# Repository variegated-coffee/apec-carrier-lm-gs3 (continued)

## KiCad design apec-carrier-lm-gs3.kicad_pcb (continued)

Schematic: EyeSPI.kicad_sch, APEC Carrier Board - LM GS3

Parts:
C1, C4, C63: 10 uF, 50V, X7R; C_1206_3216Metric; Digikey 1276-6767-1-ND
J13: Conn_02x10_Odd_Even; IDC-Header_2x10_P2.54mm_Vertical
J17: Molex 525591853; CON_525591853_MOL; LCSC C3169221
R70, R71, R72: 47R; R_0603_1608Metric; LCSC C23182

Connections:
+3V3: C1.2, J13.17, J17.1 (Vcc); also elsewhere on the board
+5V: C63.1, J13.20; also elsewhere on the board
EYESPI_BL: J13.18, J17.2 (BACKLIGHT); also elsewhere on the board
EYESPI_BUSY_TE: J13.4, J17.16 (BUSY/TE); also elsewhere on the board
EYESPI_DC: J13.11, J17.7 (DC); also elsewhere on the board
EYESPI_DISP_CS: J13.9, J17.9 (DISP_CS); also elsewhere on the board
EYESPI_GP1: J13.1, J17.17 (GPIO1); also elsewhere on the board
EYESPI_GP2: J13.2, J17.18 (GPIO2); also elsewhere on the board
EYESPI_INT: J13.3, J17.15 (INT); also elsewhere on the board
EYESPI_MEM_CS: J13.7, J17.11 (MEM_CS); also elsewhere on the board
EYESPI_MISO: R72.2; also elsewhere on the board
EYESPI_MISO_POST_R: J13.14, J17.6 (MISO), R72.1
EYESPI_MOSI: R71.1; also elsewhere on the board
EYESPI_MOSI_POST_R: J13.13, J17.5 (MOSI), R71.2
EYESPI_RES: J13.12, J17.8 (RESET); also elsewhere on the board
EYESPI_SCK: R70.2; also elsewhere on the board
EYESPI_SCK_POST_R: J13.16, J17.4 (SCK), R70.1
EYESPI_SD_CS: J13.10, J17.10 (SD_CS); also elsewhere on the board
EYESPI_TS_CS: J13.8, J17.12 (TS_CS); also elsewhere on the board
GND: C1.1, C4.2, C63.2, J13.15, J17.3 (GND); also elsewhere on the board
QWIIC_SCL: J13.5, J17.13 (SCL); also elsewhere on the board
QWIIC_SDA: J13.6, J17.14 (SDA); also elsewhere on the board
VIN: C4.1, J13.19; also elsewhere on the board

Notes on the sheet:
EyeSPI Connector

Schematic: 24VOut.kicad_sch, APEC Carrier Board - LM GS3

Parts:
C53, C54: 22 uF, 50V, X7R; C_2220_5750Metric_Pad1.97x5.40mm_HandSolder; Digikey 445-C5750X7R1H226M250KBCT-ND
C55: 100 nF, 50V, X7R; C_0603_1608Metric; LCSC C14663
CN13, CN14: Conn_01x02; TE_280370-1; LCSC C86459; not fitted
D11, D13: SS2200; D_SMA; LCSC C14332
D17, D18: LED; LED_0402_1005Metric; LCSC C130724
Q11, Q12: IRFZ44N; TO-220-3_Vertical; Digikey IRFZ44NPBF-ND
Q28: BSS138DW; SOT-363_SC-70-6; LCSC C154900
R55, R56: 10K; R_0402_1005Metric; LCSC C25744
R64, R66: 100R; R_0402_1005Metric; LCSC C25076
R73, R74: 6R8; R_0603_1608Metric; LCSC C228038
R75, R76: 100K; R_0603_1608Metric; LCSC C422892
U16: ADuM3221; SOIC-8_3.9x4.9mm_P1.27mm; LCSC C208191

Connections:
12V_ISO: U16.8 (VDD2); also elsewhere on the board
24V_STEAM_OUT: Q28.2 (G), R56.1, U16.3 (VIB); also elsewhere on the board
24V_TEA_SOLENOID: Q28.5 (G), R55.2, U16.2 (VIA); also elsewhere on the board
+3V3: C55.2, R64.1, R66.1, U16.1 (VDD1); also elsewhere on the board
+24V: C53.1, C54.1, CN13.2, CN14.2, D11.1 (K), D13.1 (K); also elsewhere on the board
GND: C55.1, Q28.1 (S), Q28.4 (S), R55.1, R56.2, U16.4 (GND1); also elsewhere on the board
GNDPWR: C53.2, C54.2, Q11.3 (S), Q12.3 (S), R75.2, R76.1, U16.5 (GND2); also elsewhere on the board
unnamed: CN13.1, D13.2 (A), Q11.2 (D)
unnamed: CN14.1, D11.2 (A), Q12.2 (D)
unnamed: D17.2 (A), R64.2
unnamed: D17.1 (K), Q28.6 (D)
unnamed: D18.2 (A), R66.2
unnamed: D18.1 (K), Q28.3 (D)
unnamed: Q11.1 (G), R73.1, R75.1
unnamed: Q12.1 (G), R74.2, R76.2
unnamed: R74.1, U16.7 (VOA)
unnamed: R73.2, U16.6 (VOB)

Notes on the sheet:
U16 is an ADuM3221 drawn with the ADuM1200 symbol. The pinouts are the same (ADuM3220/ADuM3221 datasheet).
RP2350 erratum E9 and pull-downs R55, R56: The 10K pull-downs hold these outputs low despite E9. E9 (A2 stepping only) needs a pin's input buffer on, its output off and its voltage between the logic levels. After power-up or reset the input buffer is off, so the pull-down holds the pin low, and onc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

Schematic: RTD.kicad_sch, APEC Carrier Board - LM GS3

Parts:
C5, C7, C13, C15, C21, C26: 4.7nF, C0G; C_0805_2012Metric_Pad1.18x1.45mm_HandSolder; LCSC C338091
C6, C10, C14: 47nF, C0G; C_0805_2012Metric_Pad1.18x1.45mm_HandSolder; LCSC C2182212
C30: 47 uF, 25V; C_1206_3216Metric; LCSC C76659
J8, J11: Conn_01x04; TE_280371-2; Digikey A106401-ND
JP3, JP6, JP7, JP8: SolderJumper_2_Bridged; SolderJumper-2_P1.3mm_Bridged_RoundedPad1.0x1.5mm
JP4, JP9: SolderJumper_2_Open; SolderJumper-2_P1.3mm_Open_RoundedPad1.0x1.5mm
R5: 2K2 0.01%; R_0805_2012Metric_Pad1.20x1.40mm_HandSolder; LCSC C2089922
R6, R7, R18, R20: 4K99 0.1%; R_0805_2012Metric_Pad1.20x1.40mm_HandSolder; LCSC C864414
R9: 10K; R_0805_2012Metric_Pad1.20x1.40mm_HandSolder; LCSC C17414
R34: 0R; R_0805_2012Metric_Pad1.20x1.40mm_HandSolder; LCSC C17477

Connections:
+5VA: C30.1; also elsewhere on the board
ADC_AIN0: J11.4, JP3.1 (A); also elsewhere on the board
ADC_AIN1: C5.2, C6.1, R6.2; also elsewhere on the board
ADC_AIN2: C6.2, C7.1, R7.2; also elsewhere on the board
ADC_AIN3: JP4.1 (A); also elsewhere on the board
ADC_AIN8: J8.4, JP7.1 (A); also elsewhere on the board
ADC_AIN9: C13.2, C14.1, R18.2; also elsewhere on the board
ADC_AIN10: C14.2, C15.1, R20.2; also elsewhere on the board
ADC_AIN11: JP9.1 (A); also elsewhere on the board
ADC_REFN0: C10.2, C21.1, R34.1; also elsewhere on the board
ADC_REFP0: C10.1, C26.2, R9.1; also elsewhere on the board
GNDA: C5.1, C7.2, C13.1, C15.2, C21.2, C26.1, C30.2, R5.2, R34.2; also elsewhere on the board
unnamed: J8.2, JP8.2 (B), JP9.2 (B), R20.1
unnamed: J8.3, JP7.2 (B), R18.1
unnamed: J11.2, JP4.2 (B), JP6.2 (B), R7.1
unnamed: J11.3, JP3.2 (B), R6.1
REF_R: J8.1, J11.1, JP6.1 (A), JP8.1 (A), R5.1, R9.2

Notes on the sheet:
This is basically just the reference design from TI. This filter (~323 Hz) should be frequency matched to the filter on the reference resistor (~308 Hz).
These are both configured for a two-wire PT1000 measurement. To change to three-wire or four-wire, you can cut/solder jumpers according to SBAA275A. The filter resistors and capacitors should also be changed. Similarly, to change to PT100, you can change filter resistors and capacitors.
This is part of the reference design from TI. The values for the filter and the reference resistor should be selected to match the excitation current and filter frequency (330 Hz). R1A: R_Ref (R5) = 2K2. Inputs: 2 x 4K99 into 47 nF + 2 x 4.7 nF -> ~323 Hz. Reference: REFN0 straight to R5 (R34 = 0R,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

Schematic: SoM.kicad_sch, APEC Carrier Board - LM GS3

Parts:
C27, C29: 47 uF, 25V; C_1206_3216Metric; LCSC C76659
J25: BM03B-SRSS-TBLFSN; CONN_BM03B-SRSS-TBLFSN_JST; LCSC C160389
JP10: SolderJumper_3_Open; SolderJumper-3_P1.3mm_Open_RoundedPad1.0x1.5mm_NumberLabels
R46, R47: 100R; R_0402_1005Metric; LCSC C25076
SW3, SW4, SW5, SW6: B3FS-100xP; SW_SPST_Omron_B3FS-100xP; LCSC C231324
U1: APEC_SoM; APEC_SoM_SMD
U6: Femtoprobe; Femtoprobe SMT

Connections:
24V_STEAM_OUT: U1.19 (RP2350_GP5); also elsewhere on the board
24V_TEA_SOLENOID: U1.29 (RP2350_GP43); also elsewhere on the board
+3V3: C29.2, JP10.3 (B), U1.76 (3V3), U1.77 (3V3), U6.4 (3V3); also elsewhere on the board
+5V: C27.2, U1.85 (+5V), U1.86 (+5V); also elsewhere on the board
+5VA: U1.50 (5VA); also elsewhere on the board
ADC_AIN0: U1.41 (ADC_AIN0); also elsewhere on the board
ADC_AIN1: U1.42 (ADC_AIN1); also elsewhere on the board
ADC_AIN2: U1.43 (ADC_AIN2); also elsewhere on the board
ADC_AIN3: U1.44 (ADC_AIN3); also elsewhere on the board
ADC_AIN4: U1.45 (ADC_AIN4); also elsewhere on the board
ADC_AIN5: U1.46 (ADC_AIN5); also elsewhere on the board
ADC_AIN8: U1.53 (ADC_AIN8); also elsewhere on the board
ADC_AIN9: U1.54 (ADC_AIN9); also elsewhere on the board
ADC_AIN10: U1.55 (ADC_AIN10); also elsewhere on the board
ADC_AIN11: U1.56 (ADC_AIN11); also elsewhere on the board
ADC_REFN0: U1.52 (ADC_REFN0); also elsewhere on the board
ADC_REFP0: U1.51 (ADC_REFP0); also elsewhere on the board
ADC_REFP1: U1.47 (ADC_AIN6_REFP1); also elsewhere on the board
AIN_POT_1_2V5: U1.25 (RP2350_GP47); also elsewhere on the board
AIN_POT_2_2V5: U1.26 (RP2350_GP46); also elsewhere on the board
APEC_USB_UPSTREAM_DN: U1.89 (USB_UPSTREAM_DN); also elsewhere on the board
APEC_USB_UPSTREAM_DP: U1.88 (USB_UPSTREAM_DP); also elsewhere on the board
AUX1: U1.32 (RP2350_GP40); also elsewhere on the board
BREW_BOILER_EN: U1.61 (RP2350_GP37); also elsewhere on the board
CIN3: U1.37 (CIN3); also elsewhere on the board
CIN4: U1.36 (CIN4); also elsewhere on the board
ESP32_EN: SW5.1, U1.104 (ESP32_EN)
ESP32_GP0: U1.1 (ESP32_GP0); also elsewhere on the board
ESP32_GP1: U1.2 (ESP32_GP1); also elsewhere on the board
ESP32_GPIO9: SW6.1, U1.103 (ESP32_GPIO9)
ESP32_U0RX: U1.3 (ESP32_U0RXD), U6.6 (UART_TX)
ESP32_U0TX: U1.4 (ESP32_U0TXD), U6.5 (UART_RX)
EYESPI_BL: U1.23 (RP2350_GP1); also elsewhere on the board
EYESPI_BUSY_TE: U1.6 (RP2350_GP22); also elsewhere on the board
EYESPI_DC: U1.18 (RP2350_GP6); also elsewhere on the board
EYESPI_DISP_CS: U1.16 (RP2350_GP12); also elsewhere on the board
EYESPI_GP1: U1.10 (RP2350_GP18); also elsewhere on the board
EYESPI_GP2: U1.9 (RP2350_GP19); also elsewhere on the board
EYESPI_INT: U1.7 (RP2350_GP21); also elsewhere on the board
EYESPI_MEM_CS: U1.14 (RP2350_GP14); also elsewhere on the board
EYESPI_MISO: U1.20 (RP2350_GP4); also elsewhere on the board
EYESPI_MOSI: U1.21 (RP2350_GP3); also elsewhere on the board
EYESPI_RES: U1.17 (RP2350_GP7); also elsewhere on the board
EYESPI_SCK: U1.22 (RP2350_GP2); also elsewhere on the board
EYESPI_SD_CS: U1.15 (RP2350_GP13); also elsewhere on the board
EYESPI_TS_CS: U1.13 (RP2350_GP15); also elsewhere on the board
FDC_SHLD1: U1.40 (C_SHIELD_1); also elsewhere on the board
FDC_SHLD2: U1.35 (C_SHIELD_2); also elsewhere on the board
FEMTOPROBE_USB_DN: U1.95 (USB_PORT4_DN), U6.2 (USB_D-)
FEMTOPROBE_USB_DP: U1.94 (USB_PORT4_DP), U6.3 (USB_D+)
FG_DIRECTION_3V3: U1.63 (RP2350_GP35); also elsewhere on the board
FG_SPEED_IN_3V3: U1.28 (RP2350_GP44); also elsewhere on the board
FG_TACHO_OUT_5V: U1.71 (RP2350_GP25); also elsewhere on the board
FLOW_METER_DATA: U1.73 (RP2350_GP23); also elsewhere on the board
GND: C27.1, C29.1, J25.2, JP10.1 (A), SW3.2, SW4.2, SW5.2, SW6.2, U1.5 (GND), U1.24 (GND), U1.57 (GND), U1.74 (GND), U1.90 (GND), U1.93 (GND), U1.96 (GND), U1.97 (GND), U6.1 (GND); also elsewhere on the board
GNDA: U1.48 (ADC_AIN7_REFN1), U1.49 (GNDA); also elsewhere on the board
INT_SCL: U1.33 (I2C_SCL); also elsewhere on the board
INT_SDA: U1.34 (I2C_SDA); also elsewhere on the board
INT_SPI_MISO: U1.58 (INT_SPI_MISO)
INT_SPI_MOSI: U1.60 (INT_SPI_MOSI)
INT_SPI_SCLK: U1.59 (INT_SPI_SCLK)
MP_PADDLE_SW: U1.8 (RP2350_GP20); also elsewhere on the board
NAU7802_1_DRDY_3V3: U1.27 (RP2350_GP45); also elsewhere on the board
unnamed: JP10.2 (C), U1.102 (ESP32_JTAG_SELECT)
PUMP_OUT: U1.64 (RP2350_GP34); also elsewhere on the board
QWIIC_SCL: U1.11 (RP2350_GP17); also elsewhere on the board
QWIIC_SDA: U1.12 (RP2350_GP16); also elsewhere on the board
RELAY_FILL_SOLENOID: U1.65 (RP2350_GP33); also elsewhere on the board
RELAY_GROUP_SOLENOID: U1.70 (RP2350_GP26); also elsewhere on the board
RP2350_BOOTSEL: SW3.1, U1.69 (RP2350_BOOTSEL)
RP2350_RESETn: SW4.1, U1.66 (RP2350_RESETn)
RP2350_SWCLK: R46.2, U1.68 (RP2350_SWCLK)
RP2350_SWCLK_POST_R: J25.1, R46.1, U6.8 (SWCLK)
RP2350_SWD: R47.2, U1.67 (RP2350_SWD)
RP2350_SWD_POST_R: J25.3, R47.1, U6.7 (SWDIO)
SD_CS: U1.31 (RP2350_GP41); also elsewhere on the board
SD_DET: U1.30 (RP2350_GP42); also elsewhere on the board
SERVICE_BOILER_EN: U1.62 (RP2350_GP36); also elsewhere on the board
TEA_SOLENOID_OUT: U1.72 (RP2350_GP24); also elsewhere on the board
USB_VBUS: U1.87 (USB_VBUS); also elsewhere on the board
VIN: U1.79 (VIN), U1.80 (VIN); also elsewhere on the board

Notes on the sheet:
PWM4B
RP2350 debug interfaces: J25 (SWD) and U6 (Femtoprobe). U6 connects to port 4 of the APEC SoM USB hub.
PWM3B
PWM9B
PWM10A
Internally allocated: UART1 SPI1 I2C1
UART0 PWM1
SPI1
I2C Address summary I2C0 (QWIIC_SCL/SDA, GP16/17) 0x68: DS3231 Qwiic connectors J4, J15, J16 Display connectors J13, J17 I2C1 (INT_SCL/SDA, SoM internal) 0x2A: NAU7802 (via Q30) 0x50: FDC1004 (on the SoM)
SPI0
I2C0
PWM2B
TACHO OUT has to be a PWM B pin, if you want to use the PWM to measure frequency. If so, the A pin should not be used for PWM. GP25 is a B pin.
I2C1
PWM0B
FLOW_METER_DATA has to be a PWM B pin, if you want to use the PWM to measure frequency. If so, the A pin should not be used for PWM. GP23 is a B pin.

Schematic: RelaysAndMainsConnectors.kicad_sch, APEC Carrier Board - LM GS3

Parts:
C45, C46, C47, C48: C_1206_3216Metric_Pad1.33x1.80mm_HandSolder; not fitted
D4, D5, D6, D14: LED; LED_0402_1005Metric; LCSC C130724
D8, D9, D10, D12: 1N4148WT; D_SOD-523; LCSC C83482
J2: Phoenix 1753657; TerminalBlock_Phoenix_MKDS-1,5-13_1x13_P5.00mm_Horizontal; Digikey 277-13920-ND
K1: RT314012; Relay_SPDT_Schrack-RT1-16A-FormC_RM5mm; LCSC C1524780
Q22, Q23, Q24, Q25: BSS138DW; SOT-363_SC-70-6; LCSC C154900
R39, R40, R41, R42, R58, R59, R60, R61: 100R; R_0402_1005Metric; LCSC C25076
R51, R52, R53, R54: 10K; R_0402_1005Metric; LCSC C25744
RV2, RV3, RV4, RV5: B72207S0271K101; RV_Disc_D9mm_W5.4mm_P5mm_Drill0.9mm; LCSC C125493
U9, U10, U11: ALDP112; PAN_ALD_PAN; LCSC C115718

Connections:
+3V3: R58.1, R59.1, R60.1, R61.1; also elsewhere on the board
FILL_SOLENOID: J2.10, RV3.1, U10.1
GND: C45.1, C46.1, C47.1, C48.1, Q22.1 (S), Q22.4 (S), Q23.1 (S), Q23.4 (S), Q24.1 (S), Q24.4 (S), Q25.1 (S), Q25.4 (S), R51.1, R52.1, R53.1, R54.1; also elsewhere on the board
GROUP_SOLENOID: J2.6, RV4.1, U9.1
N: J2.3, J2.4, RV2.2, RV3.2, RV4.2, RV5.1; also elsewhere on the board
unnamed: D4.2 (A), R58.2
unnamed: D4.1 (K), Q22.3 (D)
unnamed: D5.2 (A), R59.2
unnamed: D5.1 (K), Q24.6 (D)
unnamed: D6.2 (A), R60.2
unnamed: D6.1 (K), Q25.6 (D)
unnamed: D8.2 (A), Q22.6 (D), U9.3
unnamed: D9.2 (A), Q25.3 (D), U10.3
unnamed: D10.2 (A), Q24.3 (D), U11.3
unnamed: D12.2 (A), K1.A1, Q23.6 (D)
unnamed: D14.2 (A), R61.2
unnamed: D14.1 (K), Q23.3 (D)
unnamed: Q22.2 (G), Q22.5 (G), R41.2
unnamed: Q24.2 (G), Q24.5 (G), R39.2
unnamed: Q25.2 (G), Q25.5 (G), R40.2
PH: K1.11, U9.2, U10.2, U11.2; also elsewhere on the board
PH_UNFUSED: J2.1; also elsewhere on the board
PUMP_OUT: R42.2, R54.2; also elsewhere on the board
RELAY_FILL_SOLENOID: R40.1, R52.2; also elsewhere on the board
RELAY_GROUP_SOLENOID: R41.1, R51.2; also elsewhere on the board
RELAY_ROTARY_PUMP: Q23.2 (G), Q23.5 (G), R42.1
ROTARY_PUMP: J2.5, K1.14, RV5.2
TEA_SOLENOID: J2.11, RV2.1, U11.1
TEA_SOLENOID_OUT: R39.1, R53.2; also elsewhere on the board
VIN: C45.2, C46.2, C47.2, C48.2, D8.1 (K), D9.1 (K), D10.1 (K), D12.1 (K), K1.A2, U9.4, U10.4, U11.4; also elsewhere on the board

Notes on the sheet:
WARNING: MAINS VOLTAGE (110 OR 230 VAC) ON THIS SHEET. PH, PH_UNFUSED, N, ROTARY_PUMP, GROUP_SOLENOID, FILL_SOLENOID and TEA_SOLENOID are all hazardous. Treat N as live: it can carry line voltage with an unpolarised plug. Net classes 230VAC-16A and 230VAC-5A keep 2.4 mm between these nets and other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
J2 mains terminals: 1 = PH_UNFUSED, 3 and 4 = N, 5 = ROTARY_PUMP, 6 = GROUP_SOLENOID, 10 = FILL_SOLENOID, 11 = TEA_SOLENOID. Pins 2, 7, 8, 9, 12 and 13 are not connected on this board.
RP2350 erratum E9 and pull-downs R51–R54: The 10K pull-downs hold these outputs low despite E9. E9 (A2 stepping only) needs a pin's input buffer on, its output off and its voltage between the logic levels. After power-up or reset the input buffer is off, so the pull-down holds the pin low, and once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

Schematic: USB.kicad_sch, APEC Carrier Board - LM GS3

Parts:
C52: 22 nF, 100V, X7R; C_0603_1608Metric; LCSC C313105
C67, C68: 100 nF, >10V, X6S; C_0402_1005Metric; LCSC C1525
D24: ESD5Z5.0T1G; D_SOD-523; LCSC C82044
FB1: BLM18AG601SN1D; Ferrite_0603_1608Metric; LCSC C19330
FL1: ECLAMP8052P.TCT; FIL_ECLAMP8052P.TCT; PARTREV 4.10mm; LCSC C2662214
J14: GT-USB-7010ASV; USB_C_Receptacle_G-Switch_GT-USB-7010ASV; LCSC C2988369
R44, R45: 5K1; R_0402_1005Metric; LCSC C25905
R69: 1M; R_0402_1005Metric; LCSC C26083

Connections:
+3V3: C67.2, C68.2; also elsewhere on the board
APEC_USB_UPSTREAM_DN: FL1.4 (I/O-_OUT); also elsewhere on the board
APEC_USB_UPSTREAM_DP: FL1.5 (I/O+_OUT); also elsewhere on the board
GND: C52.1, C67.1, C68.1, D24.2 (A), FL1.3 (GND), J14.A1 (GND), J14.A12 (GND), J14.B1 (GND), J14.B12 (GND), R44.2, R45.2, R69.2; also elsewhere on the board
unnamed: D24.1 (K), FB1.1, J14.A4 (VBUS), J14.A9 (VBUS), J14.B4 (VBUS), J14.B9 (VBUS)
unnamed: J14.A5 (CC1), R44.1
unnamed: J14.B5 (CC2), R45.1
unnamed: C52.2, J14.S1 (SHIELD), R69.1
UNFILTERED_USB_DN: FL1.2 (I/O-_IN), J14.A7 (D-), J14.B7 (D-)
UNFILTERED_USB_DP: FL1.1 (I/O+_IN), J14.A6 (D+), J14.B6 (D+)
USB_VBUS: FB1.2; also elsewhere on the board

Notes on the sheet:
R69 and C52 tie the USB shield to GND. C52 is 100 V: an 8 kV contact discharge into the shield leaves about 55 V on it.
USB is for bench programming and debugging only. VBUS also feeds the AP3012 boost on the Power sheet, whose inductor and diode connect it straight to VIN's capacitance (about 70 uF). The plug-in inrush therefore exceeds the USB limit of 10 uF. Most ports tolerate this; if one trips its current limi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
C67 and C68 are not decoupling. They carry the USB pair's return current between planes where the pair changes layer: it runs on In3, next to the +3V3 plane on In2, but starts and ends on GND-referenced layers. Keep C67 beside the vias next to FL1, and C68 beside the vias next to the SoM.

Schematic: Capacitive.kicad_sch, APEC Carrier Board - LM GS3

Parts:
C23, C24: 68pF, C0G; C_0603_1608Metric_Pad1.08x0.95mm_HandSolder; LCSC C62782
JP12: SolderJumper_2_Bridged; SolderJumper-2_P1.3mm_Bridged2Bar_RoundedPad1.0x1.5mm
R4, R30: 100M, 75V; R_0603_1608Metric_Pad0.98x0.95mm_HandSolder; LCSC C422892
R48: 10K; R_0402_1005Metric; LCSC C25744

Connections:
BOILER_CIN: C24.2, R30.1; also elsewhere on the board
CIN3: C24.1; also elsewhere on the board
CIN4: C23.1; also elsewhere on the board
FDC_SHLD1: JP12.2 (B); also elsewhere on the board
FDC_SHLD2: JP12.1 (A); also elsewhere on the board
GND: R30.2, R48.1; also elsewhere on the board
TANK_CIN: C23.2, R4.1; also elsewhere on the board
TANK_REF: R4.2, R48.2; also elsewhere on the board

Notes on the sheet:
C23 and C24 (DC-de-biasing capacitors) are 68 pF, chosen by experimentation. They use a hand-solderable package, placed where they are easy to desolder if a different value is ever needed.
JP12 closed: SHLD1 = SHLD2. Needed for single-ended + CAPDAC (SHLD2 floats in that mode). Open only for differential use.

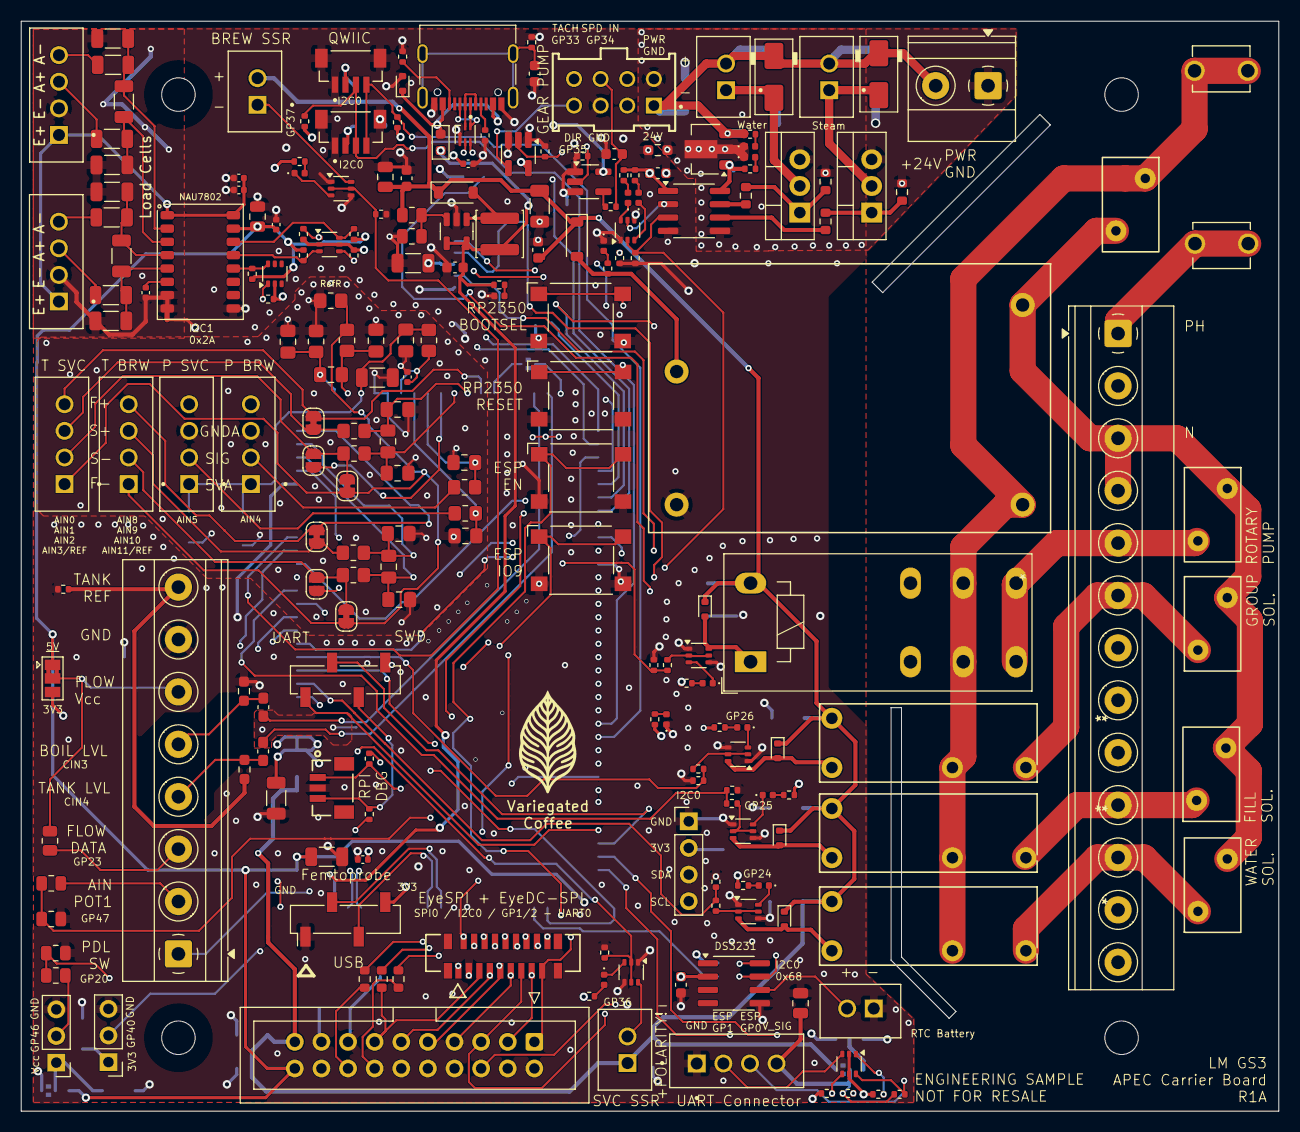
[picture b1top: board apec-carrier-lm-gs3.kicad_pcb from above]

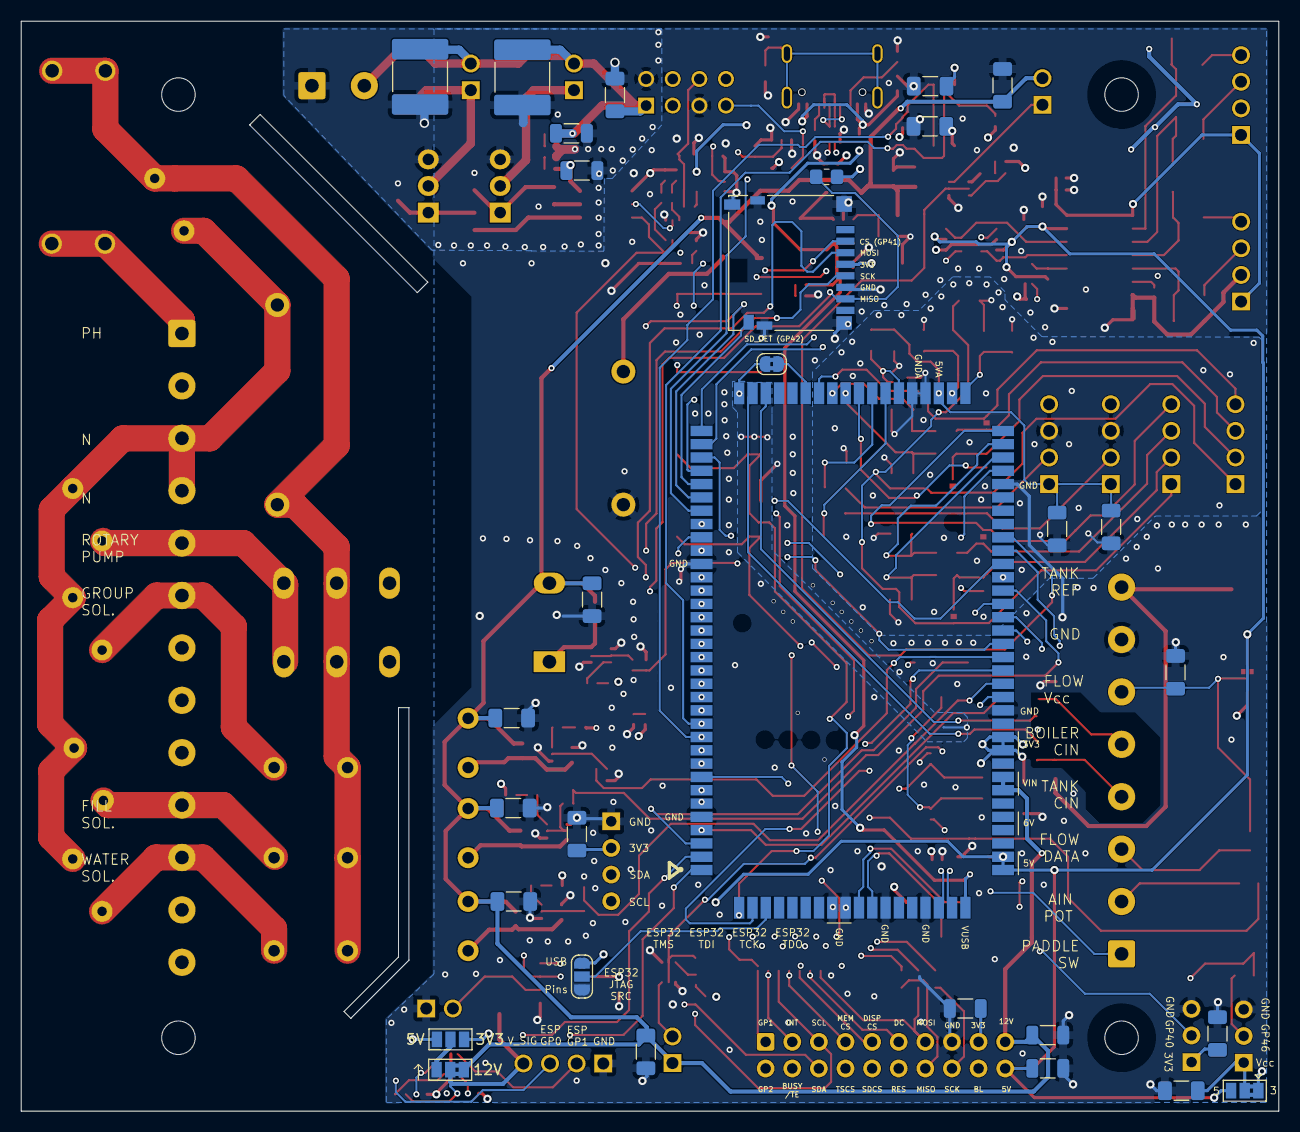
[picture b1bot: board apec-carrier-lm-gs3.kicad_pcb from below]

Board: 6 copper layers, 120.0 x 104.0 mm, 248 parts (30 on the bottom side), 173 nets.

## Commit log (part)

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2025-08-25 Initial import
2025-08-25 Add DRU
2025-09-02 As manufactured for EV1
2025-09-03 Updated parts selection
2025-09-17 Preliminary work on EV2
2025-10-26 As ordered for EV2
